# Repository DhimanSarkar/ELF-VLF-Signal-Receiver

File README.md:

# ELF Signal Receiver
A project to detect Extremely Low Frequency ([ELF](https://en.wikipedia.org/wiki/Extremely_low_frequency)) Signals

## Dependencies
- [KiCAD](https://kicad.org)

## Licences
[CERN-OHL-S](https://ohwr.org/cern_ohl_s_v2.txt)
[GNU AGPLv3](https://www.gnu.org/licenses/gpl-3.0.txt)
[CC-BY-SA-4.0](https://creativecommons.org/licenses/by-sa/4.0/legalcode)

See '[LICENCE](/LICENCE)', '[LICENCE.CERN-OHL-S.txt](/LICENCE.CERN-OHL-S.txt)', '[LICENCE.GNU-AGPLv3.txt](/LICENCE.GNU-AGPLv3.txt)', '[LICENCE.CC-BY-SA-4.0.txt](/LICENCE.CC-BY-SA-4.0.txt)' for more details.

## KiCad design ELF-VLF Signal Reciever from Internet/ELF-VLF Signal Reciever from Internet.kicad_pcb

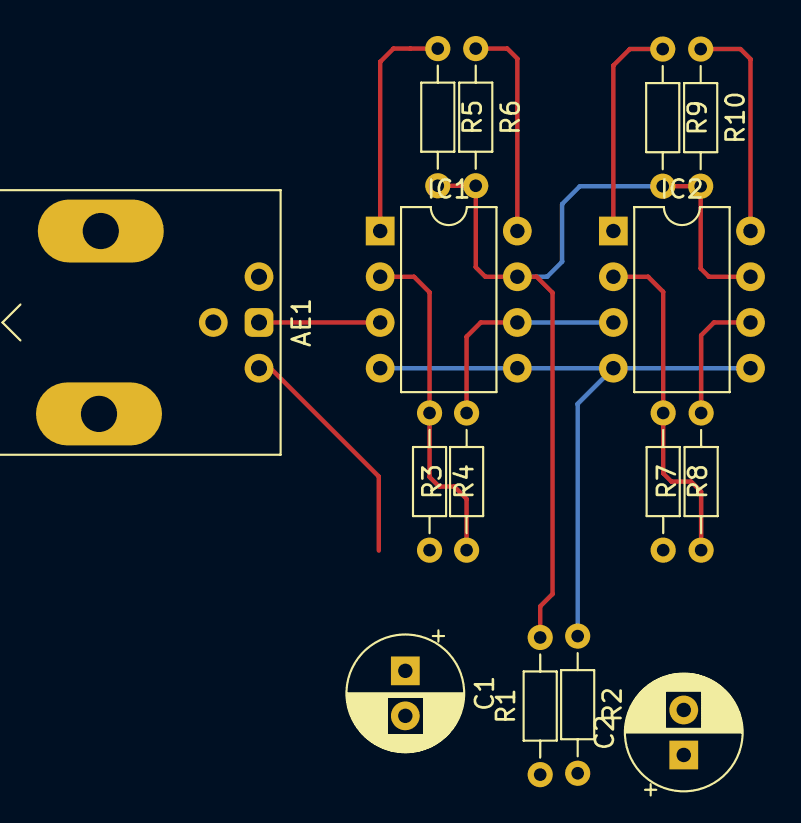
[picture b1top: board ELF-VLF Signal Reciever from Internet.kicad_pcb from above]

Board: 2 copper layers, 15 parts (0 on the bottom side), 12 nets.

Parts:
AE1: Antenna; BNC_Amphenol_031-6575_Horizontal
C1, C2: 220u; CP_Radial_D6.3mm_P2.50mm
IC1, IC2: OP27; DIP-8_W7.62mm
R1, R2: 100k; R_Axial_DIN0204_L3.6mm_D1.6mm_P7.62mm_Horizontal
R3, R7: 47k; R_Axial_DIN0204_L3.6mm_D1.6mm_P7.62mm_Horizontal
R4, R8: 2.2k; R_Axial_DIN0204_L3.6mm_D1.6mm_P7.62mm_Horizontal
R5, R6, R9, R10: 5k; R_Axial_DIN0204_L3.6mm_D1.6mm_P7.62mm_Horizontal

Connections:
GND: C2.2, IC1.4, IC1.5, IC2.4, IC2.5, R2.1
unnamed: AE1.1, IC1.3
unnamed: IC1.1, R5.1
unnamed: IC1.2, R3.1, R4.1
unnamed: IC1.6, IC2.3, R3.2
unnamed: IC1.8, R6.1
unnamed: IC2.1, R9.1
unnamed: IC2.2, R7.1, R8.1
unnamed: IC2.8, R10.1
Signal_GND: AE1.2, C1.2, C2.1, R1.1, R2.2, R4.2, R8.2
Signal_OUT: IC2.6, R7.2
VCC: C1.1, IC1.7, IC2.7, R1.2, R5.2, R6.2, R9.2, R10.2

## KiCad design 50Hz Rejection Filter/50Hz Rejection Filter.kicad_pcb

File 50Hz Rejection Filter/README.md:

# **50Hz Rejection Filter**
This analog filter has been desinged to eliminate the unwanted 50Hz Signal due to Power Transmission Systems.
The main goal is to use a Band Elimination/Rejection Filter (BEF/BRF) with high Q value.

## v1.1 - 48Hz Cut-Off Twin-T Notch Filter
The v1.1 Revision of the Filter design has a Notch Frequency of 48Hz. Which gives around -28dB Attenuation at 50Hz signal.
- ### List of Components
    1. Capacitor
        1. 0.1μF \- 4 pcs.
        2. 220μF \- 1 pcs.
    2. Resistor
        1. 33kΩ \- 4 pcs.
        2. 100kΩ \- 2 pcs.
    3. OP-AMP
        1. TL072 \- 1pcs.
            - [TL072 Datasheet](https://www.ti.com/lit/ds/slos080p/slos080p.pdf)
- ### Schematics

- ### Build Images
<div style="display: flex; flex-direction:row">
    <div style="width:100%; padding:10px"></div>
    <div style="width:100%; padding:10px"></div>
</div>

## Licences
[CERN-OHL-S](https://ohwr.org/cern_ohl_s_v2.txt)
[GNU AGPLv3](https://www.gnu.org/licenses/gpl-3.0.txt)
[CC-BY-SA-4.0](https://creativecommons.org/licenses/by-sa/4.0/legalcode)

See '[LICENCE](/LICENCE)', '[LICENCE.CERN-OHL-S.txt](/LICENCE.CERN-OHL-S.txt)', '[LICENCE.GNU-AGPLv3.txt](/LICENCE.GNU-AGPLv3.txt)', '[LICENCE.CC-BY-SA-4.0.txt](/LICENCE.CC-BY-SA-4.0.txt)' for more details.

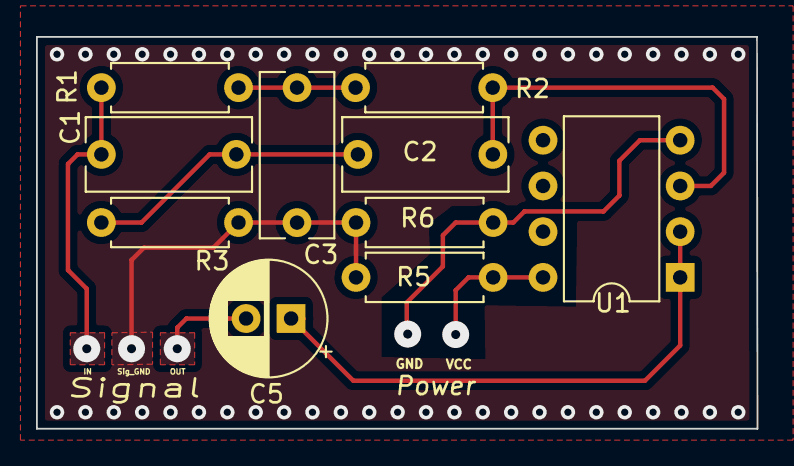
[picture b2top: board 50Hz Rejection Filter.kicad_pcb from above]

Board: 2 copper layers, 40.0 x 21.8 mm, 10 parts (0 on the bottom side), 8 nets.

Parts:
C1, C2: 0.1u; C_Rect_L9.0mm_W3.9mm_P7.50mm_MKT
C3: 0.2u; C_Rect_L9.0mm_W3.9mm_P7.50mm_MKT
C5: 220u; CP_Radial_D6.3mm_P2.50mm
R1, R2: 33k; R_Axial_DIN0207_L6.3mm_D2.5mm_P7.62mm_Horizontal
R3: 16.5k; R_Axial_DIN0207_L6.3mm_D2.5mm_P7.62mm_Horizontal
R5, R6: 100k; R_Axial_DIN0207_L6.3mm_D2.5mm_P7.62mm_Horizontal
U1: TL072; DIP-8_W7.62mm

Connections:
GND: R6.2, U1.4
GNDREF: C3.2, R3.1, R5.2, R6.1
unnamed: C1.2, C2.1, R3.2
unnamed: C2.2, R2.2, U1.3
unnamed: C3.1, R1.2, R2.1
unnamed: C5.1, U1.1, U1.2
Signal_IN: C1.1, R1.1
VCC: R5.1, U1.8

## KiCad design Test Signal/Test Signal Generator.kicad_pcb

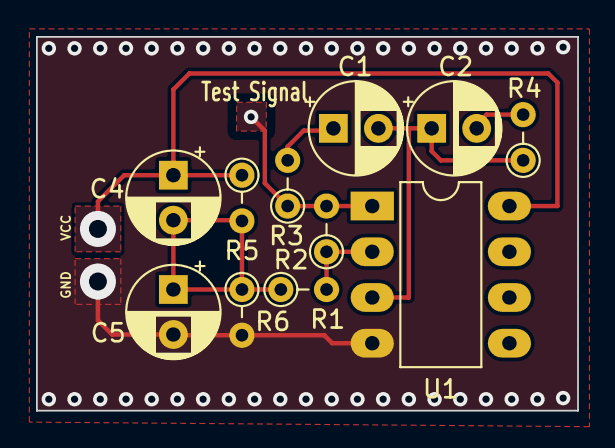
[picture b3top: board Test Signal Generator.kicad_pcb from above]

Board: 2 copper layers, 30.1 x 20.8 mm, 11 parts (0 on the bottom side), 8 nets.

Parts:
C1, C2: 1u; CP_Radial_D5.0mm_P2.50mm
C4, C5: 470u; CP_Radial_D5.0mm_P2.50mm
R1: 1k; R_Axial_DIN0204_L3.6mm_D1.6mm_P2.54mm_Vertical
R2: 2k; R_Axial_DIN0204_L3.6mm_D1.6mm_P2.54mm_Vertical
R3, R4: 18k; R_Axial_DIN0204_L3.6mm_D1.6mm_P2.54mm_Vertical
R5, R6: 100k; R_Axial_DIN0204_L3.6mm_D1.6mm_P2.54mm_Vertical
U1: TL072; DIP-8_W7.62mm_LongPads

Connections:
+5V: C4.1, R5.1, U1.8
-VDC: C5.2, R6.2, U1.4
GNDREF: C4.2, C5.1, R1.1, R5.2, R6.1
unnamed: C1.1, R3.2
unnamed: C1.2, C2.1, R4.1, U1.3
unnamed: C2.2, R4.2
unnamed: R1.2, R2.1, U1.2
Test_Signal: R2.2, R3.1, U1.1

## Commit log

2021-01-10 LICENCE - CERN-OHL-S, GNU AGPLv3, CC-BY-SA-4.0
2021-01-10 README
2021-01-10 gitignore
2021-01-10 INIT
2021-01-10 Test Signal Generator v.1
2021-01-12 Test Signal PCB Layout
2021-01-15 .gitignore
2021-01-15 Cache file deleted
2021-01-15 schematics updated, pcb updated
2021-01-19 50Hz Rejection Filter v1.1
2021-01-20 50Hz Rejection Filter v1.2 - Voltage follower Active Filter
2021-01-20 TL072 SPICE Model
2021-01-20 50Hz Rejection Filter v1.2 - PCB
2021-01-21 Signal GND Pad added
2021-01-21 v1.1 Build Images
2021-01-21 v1.1 schematics
2021-01-21 v1.1 Readme
2021-01-21 README updated
2021-01-24 External Libraries
2021-01-24 Folder name changed to Libraries
2021-01-24 VLF/ELF amplifier circuits found on internet. Slight modificationsl may have been done.
2021-03-04 Instrumentation Amplifier PreAmp
2021-03-05 Full Ckt. without testing
2021-03-05 PwrSpply Bypass Caps updated
2021-03-07 v2.1 | Filter Updated | Sheet Order updated
2021-04-25 unnecessory builds
